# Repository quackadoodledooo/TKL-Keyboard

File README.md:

# TKL Keyboard
Custom designed TKL keyboard

# PCB designed in KiCAD

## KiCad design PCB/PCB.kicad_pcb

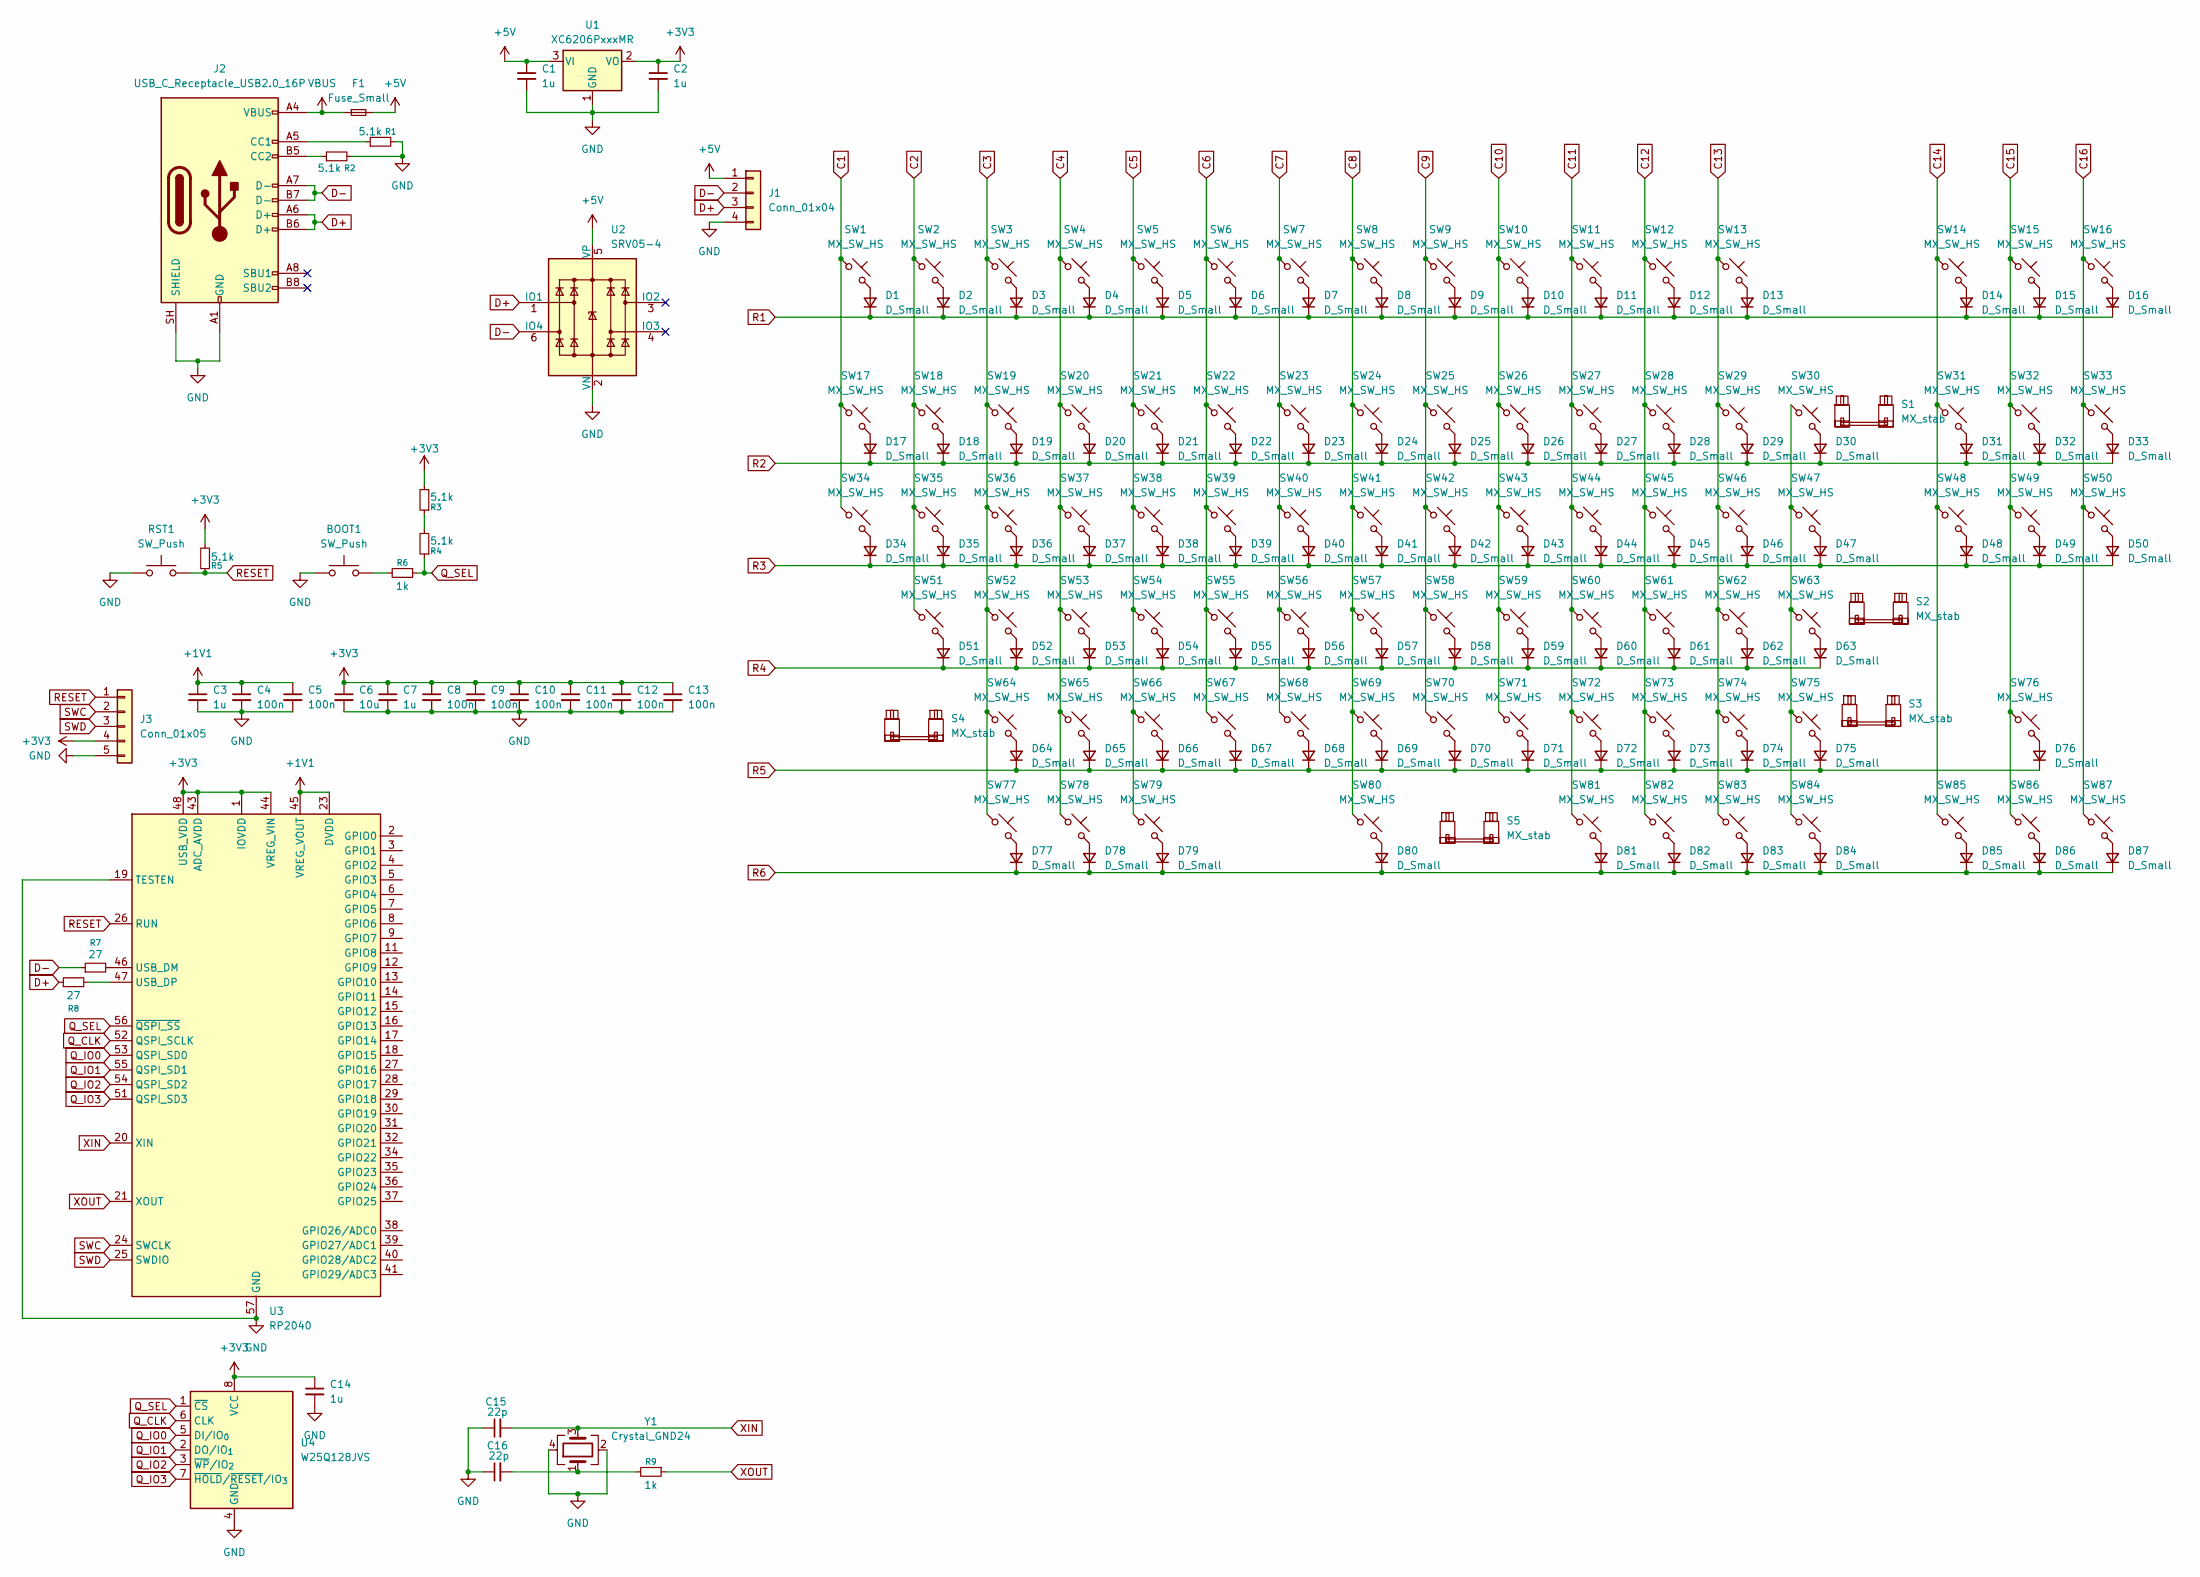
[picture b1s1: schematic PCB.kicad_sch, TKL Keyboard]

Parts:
BOOT1: SW_Push; SW_SPST_TL3342
C1, C2, C3, C7, C14: 1u; C_0402_1005Metric
C4, C5, C8, C9, C10, C11, C12, C13: 100n; C_0402_1005Metric
C6: 10u; C_0603_1608Metric
C15, C16: 22p; C_0402_1005Metric
D1, D2, D3, D4, D5, D6, D7, D8, D9, D10, D11, D12, D13, D14, D15, D16, D17, D18, D19, D20, D21, D22, D23, D24, D25, D26, D27, D28, D29, D30, D31, D32, D33, D34, D35, D36, D37, D38, D39, D40, D41, D42, D43, D44, D45, D46, D47, D48, D49, D50, D51, D52, D53, D54, D55, D56, D57, D58, D59, D60, D61, D62, D63, D64, D65, D66, D67, D68, D69, D70, D71, D72, D73, D74, D75, D76, D77, D78, D79, D80, D81, D82, D83, D84, D85, D86, D87: D_Small; D_SOD-123
F1: Fuse_Small; Fuse_1206_3216Metric
J1: Conn_01x04; JST_SH_SM04B-SRSS-TB_1x04-1MP_P1.00mm_Horizontal
J2: USB_C_Receptacle_USB2.0_16P; USB_C_Receptacle_HRO_TYPE-C-31-M-12
J3: Conn_01x05; PinHeader_1x05_P2.54mm_Vertical
R1, R2, R3, R4, R5: 5.1k; R_0402_1005Metric
R6, R9: 1k; R_0402_1005Metric
R7, R8: 27; R_0402_1005Metric
RST1: SW_Push; SW_SPST_TL3342
S1: MX_stab; STAB_MX_2u
S2, S4: MX_stab; STAB_MX_2.25u
S3: MX_stab; STAB_MX_2.75u
S5: MX_stab; STAB_MX_P_6.25u
SW1, SW2, SW3, SW4, SW5, SW6, SW7, SW8, SW9, SW10, SW11, SW12, SW13, SW14, SW15, SW16, SW17, SW18, SW19, SW20, SW21, SW22, SW23, SW24, SW25, SW26, SW27, SW28, SW29, SW30, SW31, SW32, SW33, SW35, SW36, SW37, SW38, SW39, SW40, SW41, SW42, SW43, SW44, SW45, SW46, SW48, SW49, SW50, SW52, SW53, SW54, SW55, SW56, SW57, SW58, SW59, SW60, SW61, SW62, SW63, SW64, SW65, SW66, SW67, SW68, SW69, SW70, SW71, SW72, SW73, SW74, SW75, SW76, SW80, SW85, SW86, SW87: MX_SW_HS; SW_MX_HS_CPG151101S11_1u
SW34, SW47: MX_SW_HS; SW_MX_HS_CPG151101S11_1.5u
SW51: MX_SW_HS; SW_MX_HS_CPG151101S11_1.75u
SW77, SW78, SW79, SW81, SW82, SW83, SW84: MX_SW_HS; SW_MX_HS_CPG151101S11_1.25u
U1: XC6206PxxxMR; SOT-23-3
U2: SRV05-4; SOT-23-6-routable
U3: RP2040; QFN-56-1EP_7x7mm_P0.4mm_EP3.2x3.2mm
U4: W25Q128JVS; SOIC-8_5.3x5.3mm_P1.27mm
Y1: Crystal_GND24; Crystal_SMD_3225-4Pin_3.2x2.5mm

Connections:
+1V1: C3.1, C4.1, C5.1, U3.23 (DVDD), U3.45 (VREG_VOUT), U3.50 (DVDD)
+3V3: C2.1, C6.1, C7.1, C8.1, C9.1, C10.1, C11.1, C12.1, C13.1, C14.1, J3.4, R3.2, R5.2, U1.2 (VO), U3.1 (IOVDD), U3.10 (IOVDD), U3.22 (IOVDD), U3.33 (IOVDD), U3.42 (IOVDD), U3.43 (ADC_AVDD), U3.44 (VREG_VIN), U3.48 (USB_VDD), U3.49 (IOVDD), U4.8 (VCC)
+5V: C1.1, F1.2, J1.1, U1.3 (VI), U2.5 (VP)
C1: SW1.1, SW17.1, SW34.1
C2: SW2.1, SW18.1, SW35.1, SW51.1
C3: SW3.1, SW19.1, SW36.1, SW52.1, SW64.1, SW77.1
C4: SW4.1, SW20.1, SW37.1, SW53.1, SW65.1, SW78.1
C5: SW5.1, SW21.1, SW38.1, SW54.1, SW66.1, SW79.1
C6: SW6.1, SW22.1, SW39.1, SW55.1, SW67.1
C7: SW7.1, SW23.1, SW40.1, SW56.1, SW68.1
C8: SW8.1, SW24.1, SW41.1, SW57.1, SW69.1, SW80.1
C9: SW9.1, SW25.1, SW42.1, SW58.1, SW70.1
C10: SW10.1, SW26.1, SW43.1, SW59.1, SW71.1
C11: SW11.1, SW27.1, SW44.1, SW60.1, SW72.1, SW81.1
C12: SW12.1, SW28.1, SW45.1, SW61.1, SW73.1, SW82.1
C13: SW13.1, SW29.1, SW46.1, SW62.1, SW74.1, SW83.1
C14: SW14.1, SW31.1, SW48.1, SW85.1
C15: SW15.1, SW32.1, SW49.1, SW76.1, SW86.1
C16: SW16.1, SW33.1, SW50.1, SW87.1
D+: J1.3, J2.A6 (D+), J2.B6 (D+), R8.1, U2.1 (IO1)
D-: J1.2, J2.A7 (D-), J2.B7 (D-), R7.1, U2.6 (IO4)
GND: BOOT1.1, C1.2, C2.2, C3.2, C4.2, C5.2, C6.2, C7.2, C8.2, C9.2, C10.2, C11.2, C12.2, C13.2, C14.2, C15.1, C16.1, J1.4, J2.A1 (GND), J2.A12 (GND), J2.B1 (GND), J2.B12 (GND), J2.SH (SHIELD), J3.5, R1.2, R2.2, RST1.1, U1.1 (GND), U2.2 (VN), U3.19 (TESTEN), U3.57 (GND), U4.4 (GND), Y1.2 (G), Y1.4
unnamed: BOOT1.2, R6.2
unnamed: C16.2, R9.2, Y1.1
unnamed: D1.2 (A), SW1.2
unnamed: D2.2 (A), SW2.2
unnamed: D3.2 (A), SW3.2
unnamed: D4.2 (A), SW4.2
unnamed: D5.2 (A), SW5.2
unnamed: D6.2 (A), SW6.2
unnamed: D7.2 (A), SW7.2
unnamed: D8.2 (A), SW8.2
unnamed: D9.2 (A), SW9.2
unnamed: D10.2 (A), SW10.2
unnamed: D11.2 (A), SW11.2
unnamed: D12.2 (A), SW12.2
unnamed: D13.2 (A), SW13.2
unnamed: D14.2 (A), SW14.2
unnamed: D15.2 (A), SW15.2
unnamed: D16.2 (A), SW16.2
unnamed: D17.2 (A), SW17.2
unnamed: D18.2 (A), SW18.2
unnamed: D19.2 (A), SW19.2
unnamed: D20.2 (A), SW20.2
unnamed: D21.2 (A), SW21.2
unnamed: D22.2 (A), SW22.2
unnamed: D23.2 (A), SW23.2
unnamed: D24.2 (A), SW24.2
unnamed: D25.2 (A), SW25.2
unnamed: D26.2 (A), SW26.2
unnamed: D27.2 (A), SW27.2
unnamed: D28.2 (A), SW28.2
unnamed: D29.2 (A), SW29.2
unnamed: D30.2 (A), SW30.2
unnamed: D31.2 (A), SW31.2
unnamed: D32.2 (A), SW32.2
unnamed: D33.2 (A), SW33.2
unnamed: D34.2 (A), SW34.2
unnamed: D35.2 (A), SW35.2
unnamed: D36.2 (A), SW36.2
unnamed: D37.2 (A), SW37.2
unnamed: D38.2 (A), SW38.2
unnamed: D39.2 (A), SW39.2
unnamed: D40.2 (A), SW40.2
unnamed: D41.2 (A), SW41.2
unnamed: D42.2 (A), SW42.2
unnamed: D43.2 (A), SW43.2
unnamed: D44.2 (A), SW44.2
unnamed: D45.2 (A), SW45.2
unnamed: D46.2 (A), SW46.2
unnamed: D47.2 (A), SW47.2
unnamed: D48.2 (A), SW48.2
unnamed: D49.2 (A), SW49.2
unnamed: D50.2 (A), SW50.2
unnamed: D51.2 (A), SW51.2
unnamed: D52.2 (A), SW52.2
unnamed: D53.2 (A), SW53.2
unnamed: D54.2 (A), SW54.2
unnamed: D55.2 (A), SW55.2
unnamed: D56.2 (A), SW56.2
unnamed: D57.2 (A), SW57.2
unnamed: D58.2 (A), SW58.2
unnamed: D59.2 (A), SW59.2
unnamed: D60.2 (A), SW60.2
unnamed: D61.2 (A), SW61.2
unnamed: D62.2 (A), SW62.2
unnamed: D63.2 (A), SW63.2
unnamed: D64.2 (A), SW64.2
unnamed: D65.2 (A), SW65.2
unnamed: D66.2 (A), SW66.2
unnamed: D67.2 (A), SW67.2
unnamed: D68.2 (A), SW68.2
unnamed: D69.2 (A), SW69.2
unnamed: D70.2 (A), SW70.2
unnamed: D71.2 (A), SW71.2
unnamed: D72.2 (A), SW72.2
unnamed: D73.2 (A), SW73.2
unnamed: D74.2 (A), SW74.2
unnamed: D75.2 (A), SW75.2
unnamed: D76.2 (A), SW76.2
unnamed: D77.2 (A), SW77.2
unnamed: D78.2 (A), SW78.2
unnamed: D79.2 (A), SW79.2
unnamed: D80.2 (A), SW80.2
unnamed: D81.2 (A), SW81.2
unnamed: D82.2 (A), SW82.2
unnamed: D83.2 (A), SW83.2
unnamed: D84.2 (A), SW84.2
unnamed: D85.2 (A), SW85.2
unnamed: D86.2 (A), SW86.2
unnamed: D87.2 (A), SW87.2
unnamed: J2.A5 (CC1), R1.1
unnamed: J2.B5 (CC2), R2.1
unnamed: R3.1, R4.2
unnamed: SW30.1, SW47.1, SW63.1, SW75.1, SW84.1
unnamed: R7.2, U3.46 (USB_DM)
unnamed: R8.2, U3.47 (USB_DP)
Q_CLK: U3.52 (QSPI_SCLK), U4.6 (CLK)
Q_IO0: U3.53 (QSPI_SD0), U4.5 (DI/IO_{0})
Q_IO1: U3.55 (QSPI_SD1), U4.2 (DO/IO_{1})
Q_IO2: U3.54 (QSPI_SD2), U4.3 (~WP/IO_{2})
Q_IO3: U3.51 (QSPI_SD3), U4.7 (~HOLD/~RESET/IO_{3})
Q_SEL: R4.1, R6.1, U3.56 (~QSPI_SS), U4.1 (~CS)
R1: D1.1 (K), D2.1 (K), D3.1 (K), D4.1 (K), D5.1 (K), D6.1 (K), D7.1 (K), D8.1 (K), D9.1 (K), D10.1 (K), D11.1 (K), D12.1 (K), D13.1 (K), D14.1 (K), D15.1 (K), D16.1 (K)
R2: D17.1 (K), D18.1 (K), D19.1 (K), D20.1 (K), D21.1 (K), D22.1 (K), D23.1 (K), D24.1 (K), D25.1 (K), D26.1 (K), D27.1 (K), D28.1 (K), D29.1 (K), D30.1 (K), D31.1 (K), D32.1 (K), D33.1 (K)
R3: D34.1 (K), D35.1 (K), D36.1 (K), D37.1 (K), D38.1 (K), D39.1 (K), D40.1 (K), D41.1 (K), D42.1 (K), D43.1 (K), D44.1 (K), D45.1 (K), D46.1 (K), D47.1 (K), D48.1 (K), D49.1 (K), D50.1 (K)
R4: D51.1 (K), D52.1 (K), D53.1 (K), D54.1 (K), D55.1 (K), D56.1 (K), D57.1 (K), D58.1 (K), D59.1 (K), D60.1 (K), D61.1 (K), D62.1 (K), D63.1 (K)
R5: D64.1 (K), D65.1 (K), D66.1 (K), D67.1 (K), D68.1 (K), D69.1 (K), D70.1 (K), D71.1 (K), D72.1 (K), D73.1 (K), D74.1 (K), D75.1 (K), D76.1 (K)
R6: D77.1 (K), D78.1 (K), D79.1 (K), D80.1 (K), D81.1 (K), D82.1 (K), D83.1 (K), D84.1 (K), D85.1 (K), D86.1 (K), D87.1 (K)
RESET: J3.1, R5.1, RST1.2, U3.26 (RUN)
SWC: J3.2, U3.24 (SWCLK)
SWD: J3.3, U3.25 (SWDIO)
VBUS: F1.1, J2.A4 (VBUS), J2.A9 (VBUS), J2.B4 (VBUS), J2.B9 (VBUS)
XIN: C15.2, U3.20 (XIN), Y1.3
XOUT: R9.1, U3.21 (XOUT)

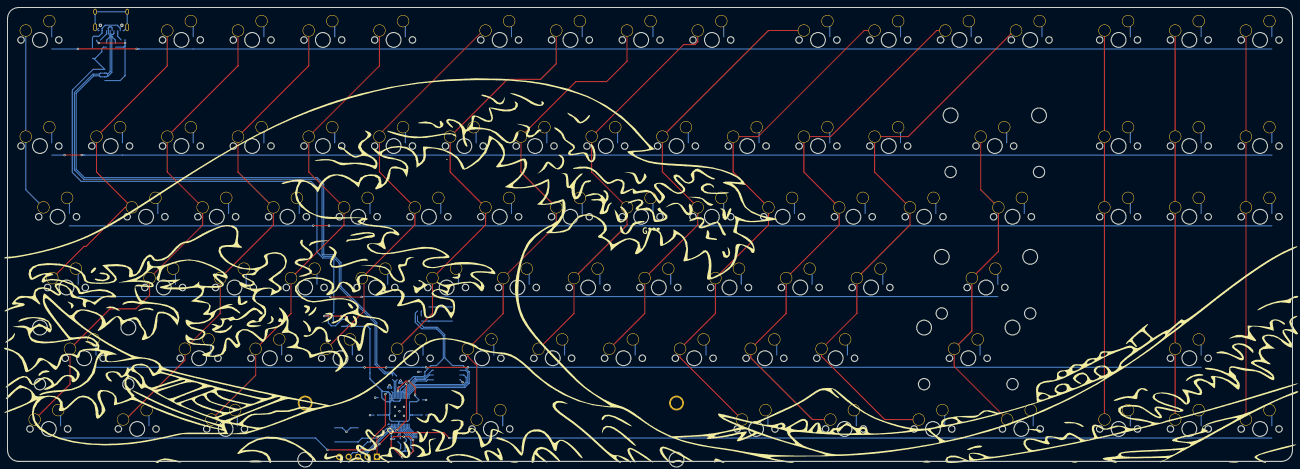
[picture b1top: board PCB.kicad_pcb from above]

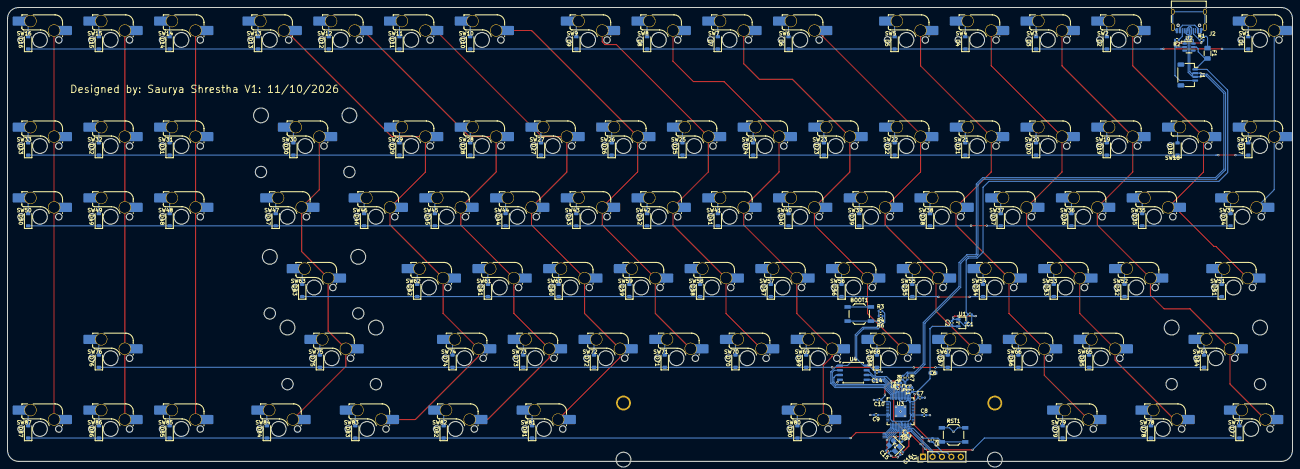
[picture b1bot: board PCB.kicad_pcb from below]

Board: 2 copper layers, 346.1 x 122.2 mm, 215 parts (215 on the bottom side), 135 nets.
